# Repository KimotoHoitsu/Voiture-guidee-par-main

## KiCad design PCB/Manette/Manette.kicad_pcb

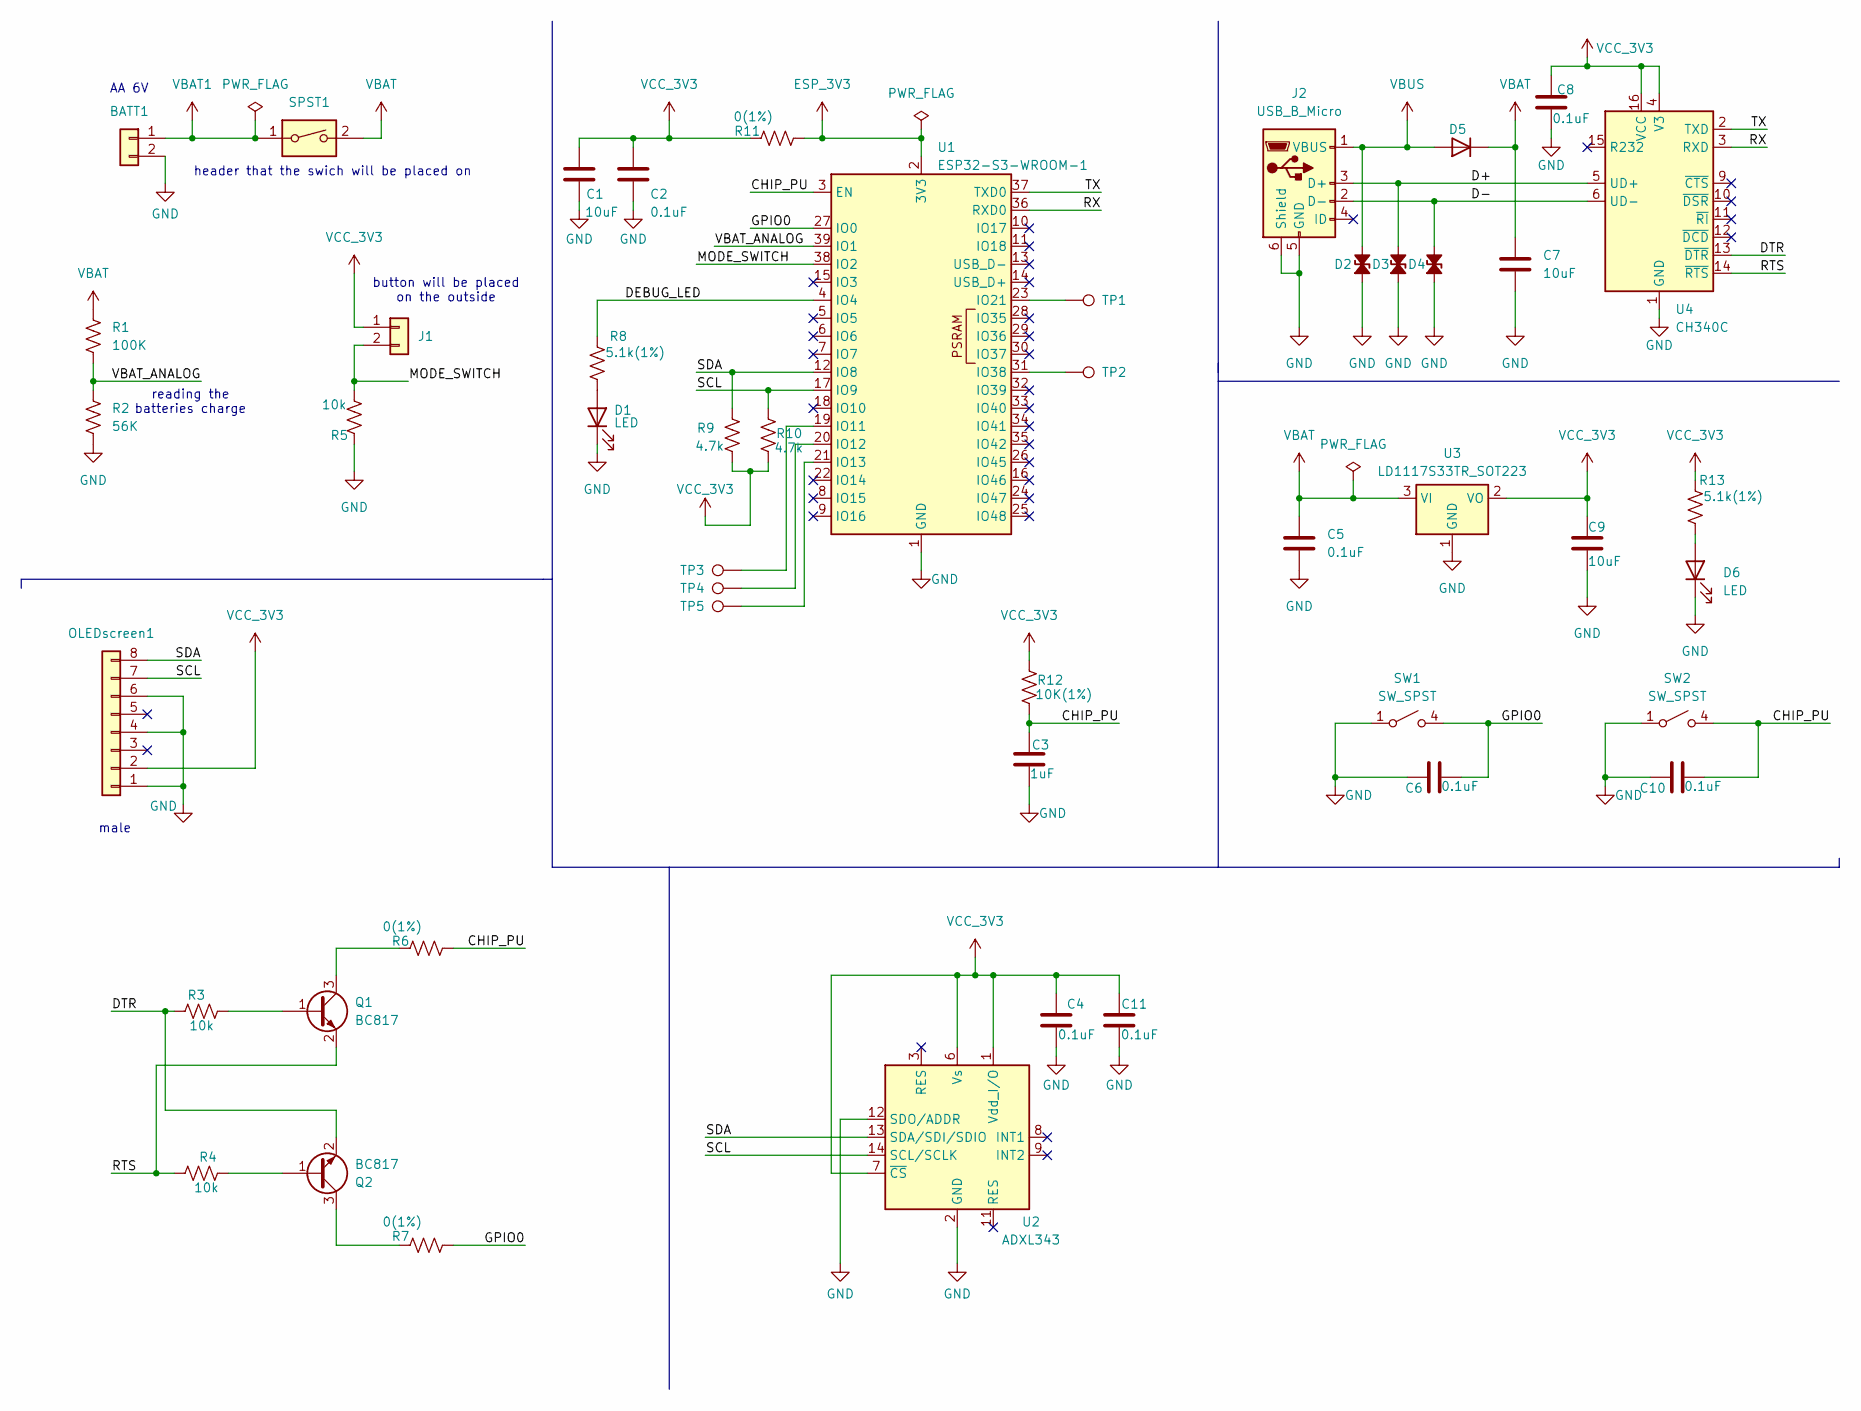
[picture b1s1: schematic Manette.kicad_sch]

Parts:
BATT1: 9V; PinHeader_1x02_P2.54mm_Vertical
C1, C7, C9: 10uF; C_0805_2012Metric
C2, C4, C5, C6, C8, C10, C11: 0.1uF; C_0805_2012Metric
C3: 1uF; C_0805_2012Metric
D1, D6: LED; LED_0805_2012Metric
D2, D3, D4: DiodeZz
D5: 1N5819HW-7-F_DIO-L
J1: SPST; PinHeader_1x02_P2.54mm_Vertical
J2: USB_B_Micro; Micro_Usb
OLEDscreen1: Conn_01x08; PinHeader_1x08_P2.54mm_Vertical
Q1, Q2: BC817; SOT-23
R1: 100K; R_0805_2012Metric
R2: 56K; R_0805_2012Metric
R3, R4, R5: 10k; R_0805_2012Metric
R6, R7, R11: 0(1%); R_0805_2012Metric
R8, R13: 5.1k(1%); R_0805_2012Metric
R9, R10: 4.7k; R_0805_2012Metric
R12: 10K(1%); R_0805_2012Metric
SPST1: SW_DIP_x01; PinHeader_1x02_P2.54mm_Vertical
SW1: SW_SPST; switch
SW2: SW_SPST; switch; MPN 1825910-6
TP1, TP2: TestPoint; testpoint
TP3, TP4, TP5: TestPoint; TestPoint_Pad_D1.0mm
U1: ESP32-S3-WROOM-1
U2: ADXL343; LGA-14_3x5mm_P0.8mm_LayoutBorder1x6y
U3: LD1117S33TR_SOT223; SOT-223-3_TabPin2
U4: CH340C; SOIC-16_3.9x9.9mm_P1.27mm

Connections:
/CHIP_PU: C3.1, C10.2, R6.2, R12.2, SW2.4 (B), U1.3 (EN)
/D+: D3.2 (A2), J2.3 (D+), U4.5 (UD+)
/D-: D4.2 (A2), J2.2 (D-), U4.6 (UD-)
/DEBUG_LED: R8.2, U1.4 (IO4)
/DTR: Q2.2 (E), R3.2, U4.13 (~DTR)
/GPIO0: C6.2, R7.2, SW1.4 (B), U1.27 (IO0)
/MODE_SWITCH: J1.2, R5.2, U1.38 (IO2)
/RTS: Q1.2 (E), R4.1, U4.14 (~RTS)
/RX: U1.36 (RXD0), U4.3 (RXD)
/SCL: OLEDscreen1.7 (CLK), R10.1, U1.17 (IO9), U2.14 (SCL/SCLK)
/SDA: OLEDscreen1.8 (DATA), R9.1, U1.12 (IO8), U2.13 (SDA/SDI/SDIO)
/TX: U1.37 (TXD0), U4.2 (TXD)
/VBAT_ANALOG: R1.1, R2.2, U1.39 (IO1)
ESP_3V3: R11.2, U1.2 (3V3)
GND: BATT1.2, C1.2, C2.2, C3.2, C4.1, C5.2, C6.1, C7.2, C8.2, C9.2, C10.1, C11.1, D1.1 (K), D2.1 (A1), D3.1 (A1), D4.1 (A1), D6.1 (K), J2.5 (GND), J2.6 (Shield), OLEDscreen1.1 (GND), OLEDscreen1.4 (CS), OLEDscreen1.6 (DC), R2.1, R5.1, SW1.1 (A), SW2.1 (A), U1.1 (GND), U1.40 (GND), U1.41 (GND), U2.2 (GND), U2.4 (GND), U2.5 (GND), U2.12 (SDO/ADDR), U3.1 (GND), U4.1 (GND)
unnamed: D1.2 (A), R8.1
unnamed: D6.2 (A), R13.1
unnamed: Q1.1 (B), R3.1
unnamed: Q1.3 (C), R6.1
unnamed: Q2.1 (B), R4.2
unnamed: Q2.3 (C), R7.1
unnamed: TP3.1, U1.19 (IO11)
unnamed: TP4.1, U1.20 (IO12)
unnamed: TP5.1, U1.21 (IO13)
unnamed: TP1.1, U1.23 (IO21)
unnamed: TP2.1, U1.31 (IO38)
VBAT: C5.1, C7.1, D5.1 (K), R1.2, SPST1.2, U3.3 (VI)
VBAT1: BATT1.1, SPST1.1
VBUS: D2.2 (A2), D5.2 (A), J2.1 (VBUS)
VCC_3V3: C1.1, C2.1, C4.2, C8.1, C9.1, C11.2, J1.1, OLEDscreen1.2 (Vin), R9.2, R10.2, R11.1, R12.1, R13.2, U2.1 (Vdd_I/O), U2.6 (Vs), U2.7 (~CS), U3.2 (VO), U4.4 (V3), U4.16 (VCC)

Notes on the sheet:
reading the batteries charge
male
AA 6V
button will be placed on the outside
header that the swich will be placed on

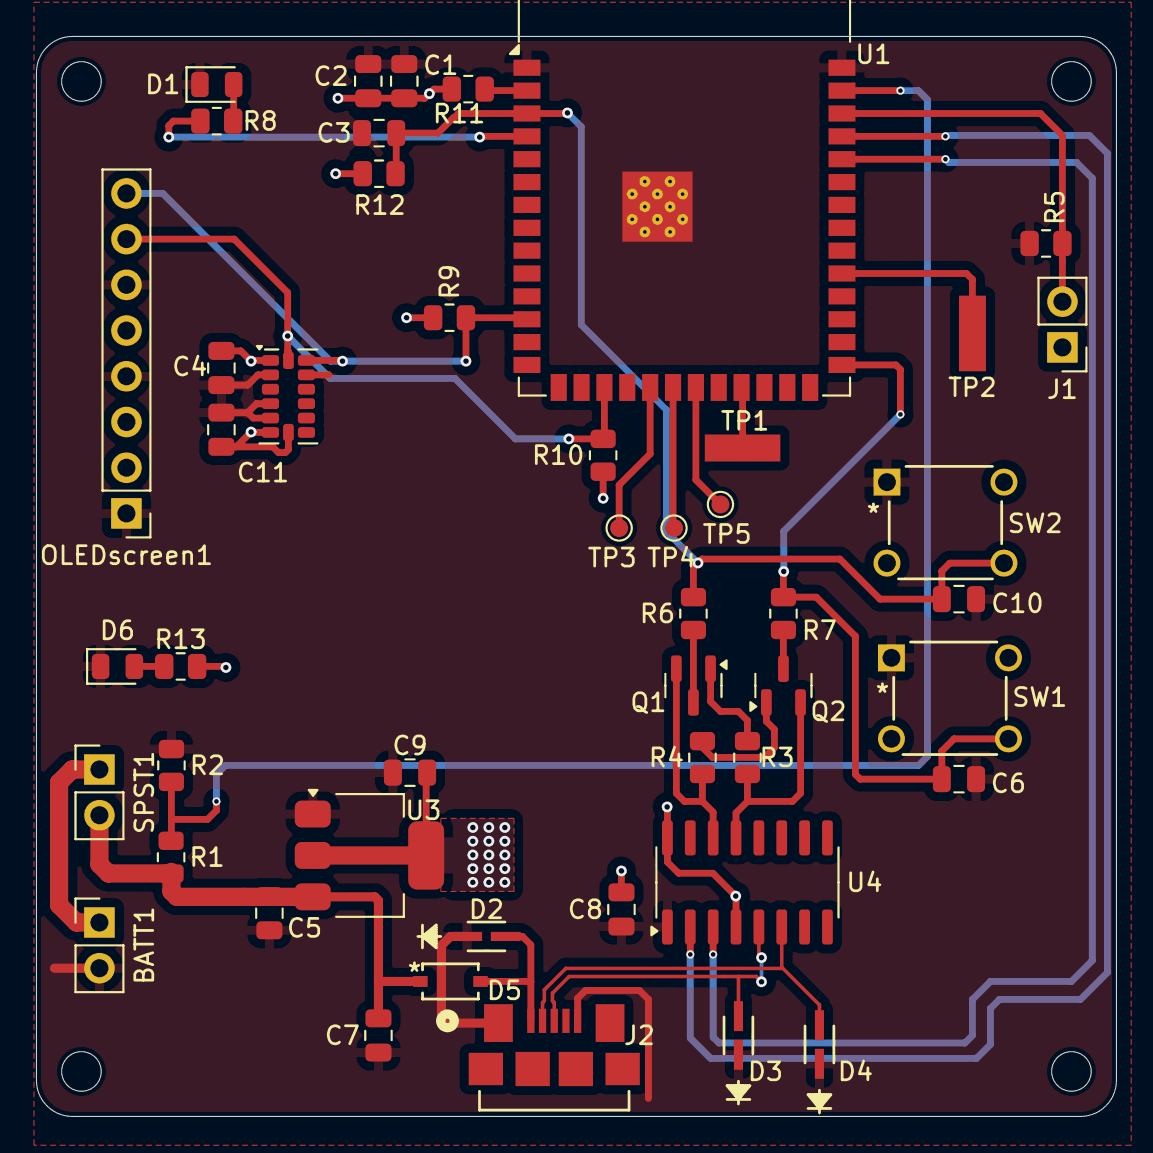
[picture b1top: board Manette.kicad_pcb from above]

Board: 2 copper layers, 60.0 x 60.0 mm, 52 parts (0 on the bottom side), 30 nets.

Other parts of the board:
H1, H2, H3, H4: MountingHole_2.2mm_M2

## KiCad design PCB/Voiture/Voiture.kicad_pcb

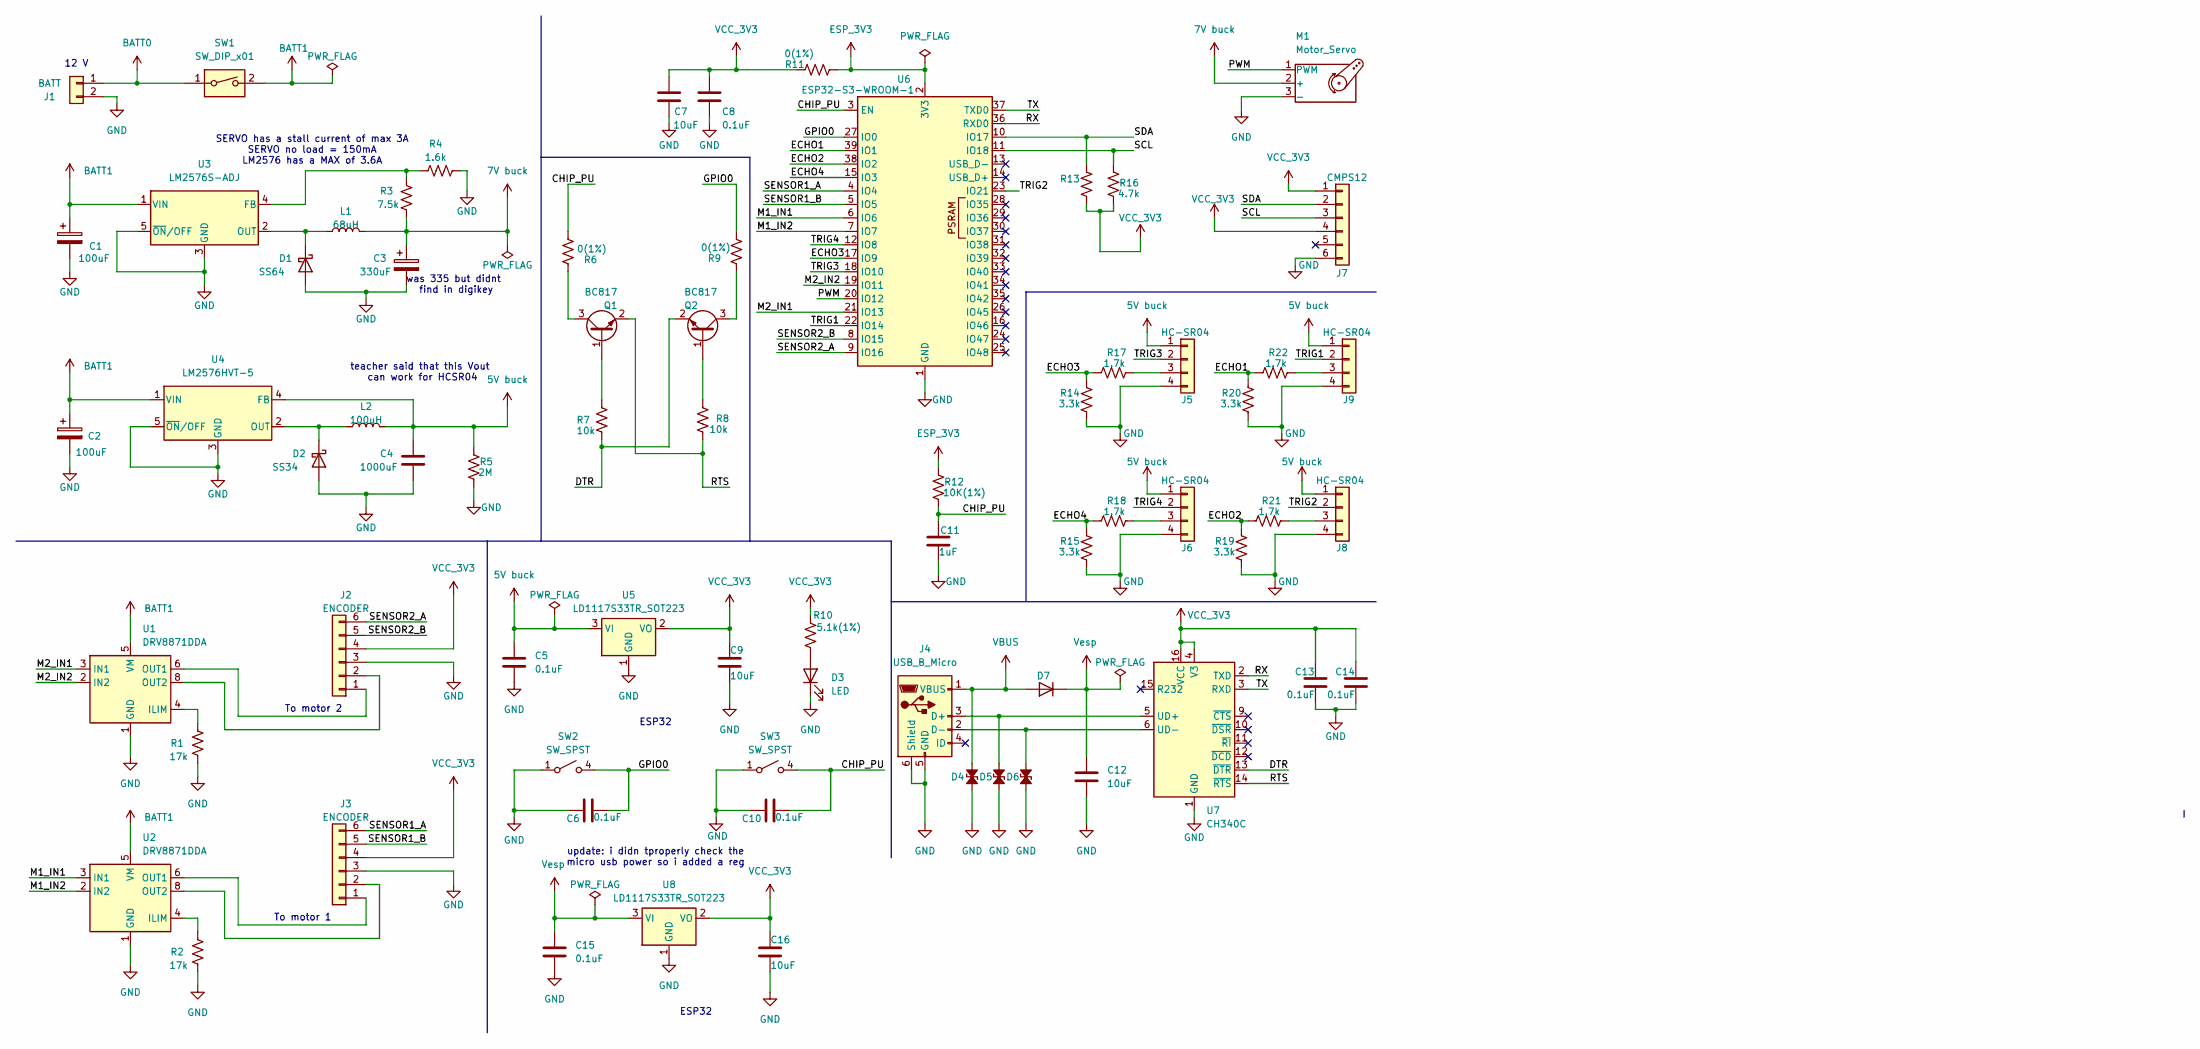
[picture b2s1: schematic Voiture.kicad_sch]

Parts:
C1, C2: 100uF; CAP_E61_CHC-M
C3: 330uF; CAP_APXG160ARA331MH70G
C4: 1000uF; CAP_A768MS_KEM-M
C5, C6, C8, C10, C13, C14, C15: 0.1uF; C_0805_2012Metric
C7, C9, C12, C16: 10uF; C_0805_2012Metric
C11: 1uF; C_0805_2012Metric
D1: SS64; ss34
D2: SS34; ss34
D3: LED; LED_0805_2012Metric
D4, D5, D6: DiodeZz
D7: 1N5819HW-7-F_DIO-L
J1: BATT; CONN_1935310_PXC
J2, J3: ENCODER; PinHeader_1x06_P2.54mm_Vertical
J4: USB_B_Micro; Micro_Usb
J5, J6, J8, J9: HC-SR04; PinHeader_1x04_P2.54mm_Vertical
J7: CMPS12; PinHeader_1x06_P2.54mm_Vertical
L1: 68uH; IND_DR127_EAT
L2: 100uH; DR127
M1: Motor_Servo; PinHeader_1x03_P2.54mm_Vertical
Q1, Q2: BC817; SOT-23
R1, R2: 17k; R_0805_2012Metric
R3: 7.5k; R_0805_2012Metric
R4: 1.6k; R_0805_2012Metric
R5: 2M; R_0805_2012Metric
R6, R9, R11: 0(1%); R_0805_2012Metric
R7, R8: 10k; R_0805_2012Metric
R10: 5.1k(1%); R_0805_2012Metric
R12: 10K(1%); R_0805_2012Metric
R13, R16: 4.7k; R_0805_2012Metric
R14, R15, R19, R20: 3.3k; R_0805_2012Metric
R17, R18, R21, R22: 1.7k; R_0805_2012Metric
SW1: SW_DIP_x01; PinHeader_1x02_P2.54mm_Vertical
SW2, SW3: SW_SPST; switch
U1, U2: DRV8871DDA; Texas_HTSOP-8-1EP_3.9x4.9mm_P1.27mm_EP2.95x4.9mm_Mask2.4x3.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
U3: LM2576S-ADJ; VREG_TPS79625KTTR
U4: LM2576HVT-5; TO-220-5_Vertical
U5, U8: LD1117S33TR_SOT223; SOT-223-3_TabPin2
U6: ESP32-S3-WROOM-1
U7: CH340C; SOIC-16_3.9x9.9mm_P1.27mm

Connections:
5V buck: C4.1, C5.1, J5.1 (VCC), J6.1 (VCC), J8.1 (VCC), J9.1 (VCC), L2.2, R5.1, U4.4 (FB), U5.3 (VI)
7V buck: C3.1, C3.P, L1.2, M1.2 (+), R3.2
/CHIP_PU: C10.2, C11.1, R6.2, R12.2, SW3.4 (B), U6.3 (EN)
/DTR: Q2.2 (E), R7.2, U7.13 (~DTR)
/ECHO1: R20.1, R22.1, U6.39 (IO1)
/ECHO2: R19.1, R21.1, U6.38 (IO2)
/ECHO3: R14.1, R17.1, U6.17 (IO9)
/ECHO4: R15.1, R18.1, U6.15 (IO3)
/GPIO0: C6.2, R9.2, SW2.4 (B), U6.27 (IO0)
/M1_IN1: U2.3 (IN1), U6.6 (IO6)
/M1_IN2: U2.2 (IN2), U6.7 (IO7)
/M2_IN1: U1.3 (IN1), U6.21 (IO13)
/M2_IN2: U1.2 (IN2), U6.19 (IO11)
/PWM: M1.1 (PWM), U6.20 (IO12)
/RTS: Q1.2 (E), R8.1, U7.14 (~RTS)
/RX: U6.36 (RXD0), U7.2 (TXD)
/SCL: J7.3 (SCL), R16.1, U6.11 (IO18)
/SDA: J7.2 (SDA), R13.1, U6.10 (IO17)
/SENSOR1_A: J3.6 (SENSORsigA), U6.4 (IO4)
/SENSOR1_B: J3.5 (SENSORsigB), U6.5 (IO5)
/SENSOR2_A: J2.6 (SENSORsigA), U6.9 (IO16)
/SENSOR2_B: J2.5 (SENSORsigB), U6.8 (IO15)
/TRIG1: J9.2 (Trig), U6.22 (IO14)
/TRIG2: J8.2 (Trig), U6.23 (IO21)
/TRIG3: J5.2 (Trig), U6.18 (IO10)
/TRIG4: J6.2 (Trig), U6.12 (IO8)
/TX: U6.37 (TXD0), U7.3 (RXD)
BATT0: J1.1, SW1.1
BATT1: C1.1, C2.1, SW1.2, U1.5 (VM), U2.5 (VM), U3.1 (VIN), U4.1 (VIN)
ESP_3V3: R11.2, R12.1, U6.2 (3V3)
GND: C1.2, C2.2, C3.2, C3.N, C4.2, C5.2, C6.1, C7.2, C8.2, C9.2, C10.1, C11.2, C12.2, C13.2, C14.2, C15.2, C16.2, D1.2 (A), D2.2 (A), D3.1 (K), D4.1 (A1), D5.1 (A1), D6.1 (A1), J1.2, J2.3 (SENSOR_GND), J3.3 (SENSOR_GND), J4.5 (GND), J4.6 (Shield), J5.4 (GND), J6.4 (GND), J7.6 (GND), J8.4 (GND), J9.4 (GND), M1.3 (-), R1.1, R2.1, R4.2, R5.2, R14.2, R15.2, R19.2, R20.2, SW2.1 (A), SW3.1 (A), U1.1 (GND), U1.7 (GND), U1.9 (GND), U2.1 (GND), U2.7 (GND), U2.9 (GND), U3.3 (GND), U3.5 (~ON/OFF), U4.3 (GND), U4.5 (~ON/OFF), U5.1 (GND), U6.1 (GND), U6.40 (GND), U6.41 (GND), U7.1 (GND), U8.1 (GND)
unnamed: D1.1 (K), L1.1, U3.2 (OUT)
unnamed: D2.1 (K), L2.1, U4.2 (OUT)
unnamed: D3.2 (A), R10.1
unnamed: D5.2 (A2), J4.3 (D+), U7.5 (UD+)
unnamed: D6.2 (A2), J4.2 (D-), U7.6 (UD-)
unnamed: J2.2 (MOTOR-), U1.8 (OUT2)
unnamed: J2.1 (MOTOR_+), U1.6 (OUT1)
unnamed: J3.2 (MOTOR-), U2.8 (OUT2)
unnamed: J3.1 (MOTOR_+), U2.6 (OUT1)
unnamed: J5.3 (Echo), R17.2
unnamed: J6.3 (Echo), R18.2
unnamed: J8.3 (Echo), R21.2
unnamed: J9.3 (Echo), R22.2
unnamed: Q1.1 (B), R7.1
unnamed: Q1.3 (C), R6.1
unnamed: Q2.1 (B), R8.2
unnamed: Q2.3 (C), R9.1
unnamed: R1.2, U1.4 (ILIM)
unnamed: R2.2, U2.4 (ILIM)
unnamed: R3.1, R4.1, U3.4 (FB)
VBUS: D4.2 (A2), D7.2 (A), J4.1 (VBUS)
VCC_3V3: C7.1, C8.1, C9.1, C13.1, C14.1, C16.1, J2.4 (VCC(5V5)), J3.4 (VCC(5V5)), J7.1 (Vin), J7.4 (Mode), R10.2, R11.1, R13.2, R16.2, U5.2 (VO), U7.4 (V3), U7.16 (VCC), U8.2 (VO)
Vesp: C12.1, C15.1, D7.1 (K), U8.3 (VI)

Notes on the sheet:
ESP32
To motor 2
To motor 1
teacher said that this Vout can work for HCSR04
was 335 but didnt find in digikey
update: i didn tproperly check the micro usb power so i added a reg
12 V
SERVO has a stall current of max 3A SERVO no load = 150mA LM2576 has a MAX of 3.6A

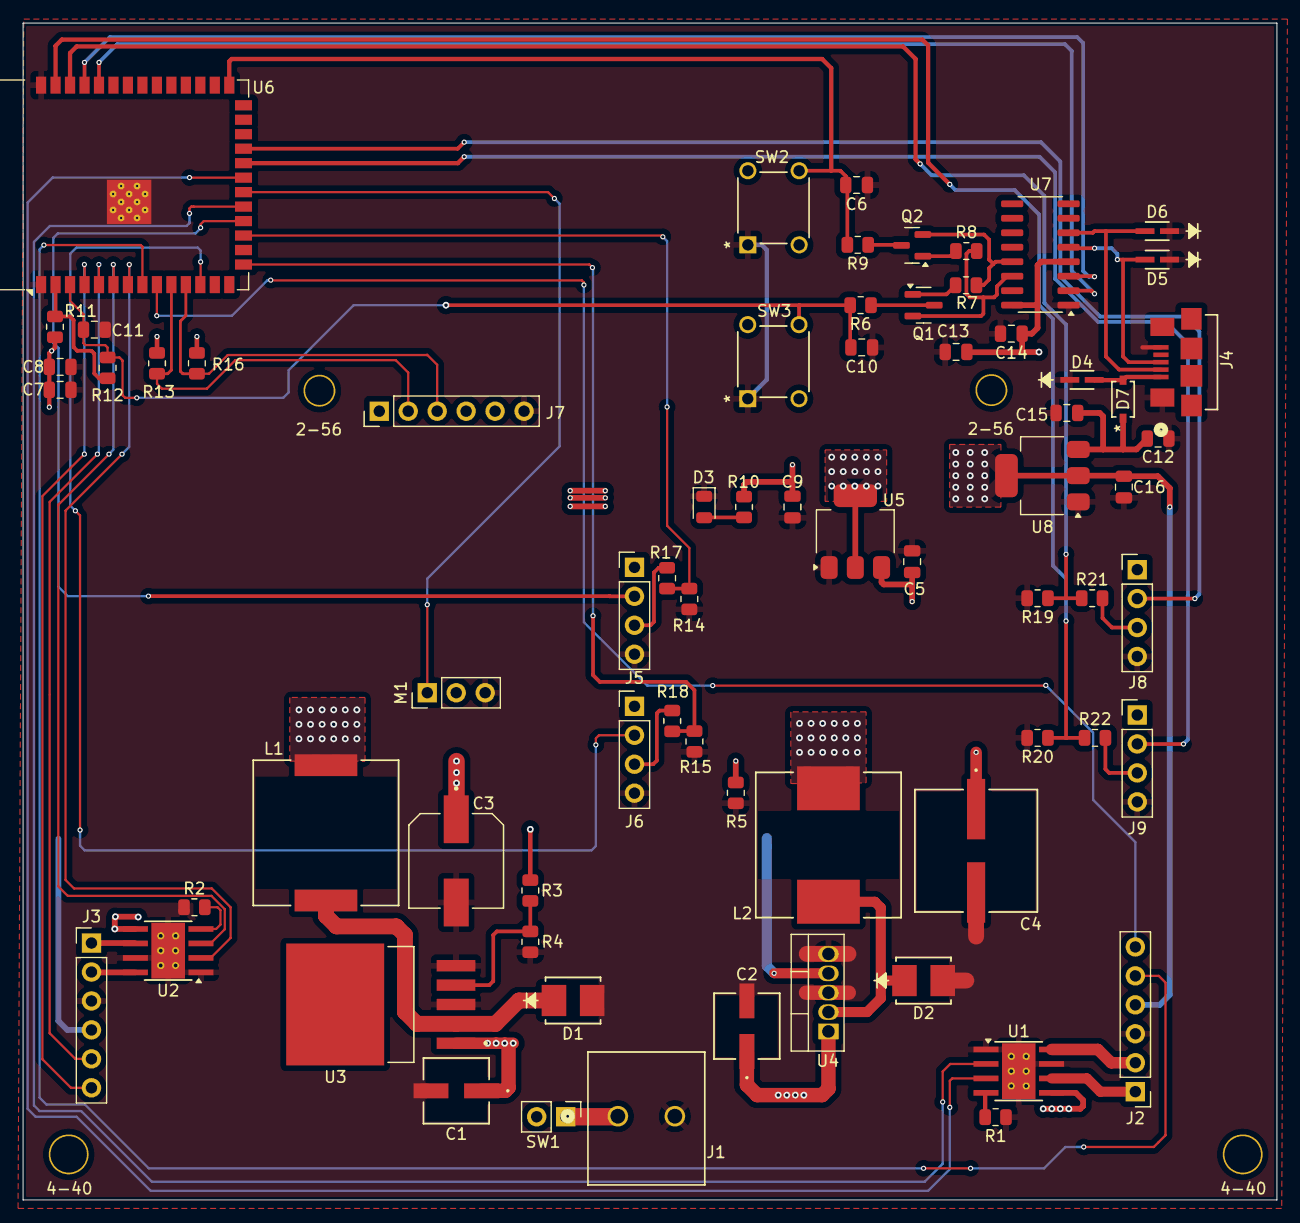
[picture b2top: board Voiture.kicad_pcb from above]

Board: 2 copper layers, 110.0 x 103.2 mm, 74 parts (0 on the bottom side), 54 nets.

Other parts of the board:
2-56, 2-56#2: MountingHole_2.5mm
4-40, 4-40#2: MountingHole_3.2mm_M3
